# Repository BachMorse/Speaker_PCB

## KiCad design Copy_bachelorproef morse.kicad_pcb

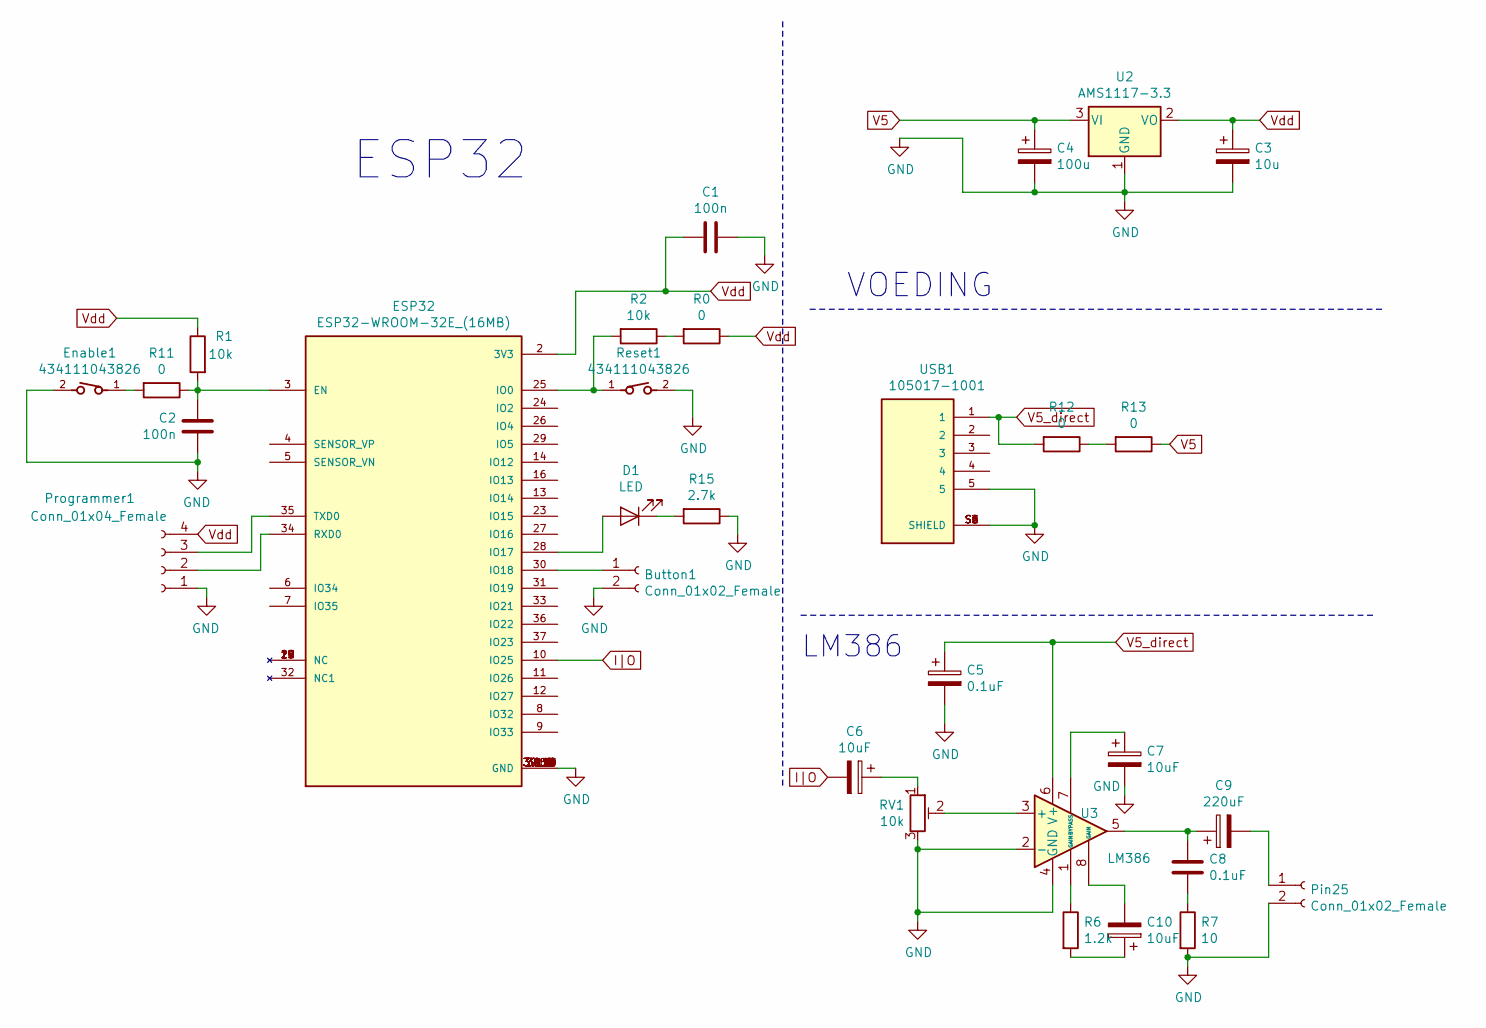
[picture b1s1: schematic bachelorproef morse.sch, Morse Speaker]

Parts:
Button1: Conn_01x02_Female; PinSocket_1x02_P2.54mm_Vertical
C1, C2: 100n; C_1206_3216Metric_Pad1.42x1.75mm_HandSolder
C3: 10u; C_1206_3216Metric_Pad1.42x1.75mm_HandSolder
C4: 100u; C_1206_3216Metric_Pad1.42x1.75mm_HandSolder
C5, C8: 0.1uF; C_1206_3216Metric_Pad1.42x1.75mm_HandSolder
C6, C7, C10: 10uF; C_1206_3216Metric_Pad1.42x1.75mm_HandSolder
C9: 220uF; C_1206_3216Metric_Pad1.42x1.75mm_HandSolder
D1: LED; R_1206_3216Metric_Pad1.42x1.75mm_HandSolder
ESP32: ESP32-WROOM-32E_(16MB); MODULE_ESP32-WROOM-32E_(16MB)
Enable1: 434111043826
Pin25: Conn_01x02_Female; PinSocket_1x02_P2.54mm_Vertical
Programmer1: Conn_01x04_Female; PinSocket_1x04_P2.54mm_Vertical
R0, R11, R12, R13: 0; R_1206_3216Metric_Pad1.42x1.75mm_HandSolder
R1, R2: 10k; R_1206_3216Metric_Pad1.42x1.75mm_HandSolder
R6: 1.2k; R_1206_3216Metric_Pad1.42x1.75mm_HandSolder
R7: 10; R_1206_3216Metric_Pad1.42x1.75mm_HandSolder
R15: 2.7k; R_1206_3216Metric_Pad1.42x1.75mm_HandSolder
RV1: 10k; Potentiometer_Bourns_3224G_Horizontal
Reset1: 434111043826
U2: AMS1117-3.3; SOT-223-3_TabPin2
U3: LM386; DIP794W45P254L959H508Q8
USB1: 105017-1001; MOLEX_105017-1001

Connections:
GND: Button1.2, C1.1, C2.2, C3.2, C4.2, C5.2, C7.2, ESP32.1 (GND), ESP32.15 (GND), ESP32.38 (GND), ESP32.39_1 (GND), ESP32.39_2 (GND), ESP32.39_3 (GND), ESP32.39_4 (GND), ESP32.39_5 (GND), ESP32.39_6 (GND), ESP32.39_7 (GND), ESP32.39_8 (GND), ESP32.39_9 (GND), ESP32.39_10 (GND), ESP32.39_11 (GND), ESP32.39_12 (GND), ESP32.39_13 (GND), ESP32.39_14 (GND), ESP32.39_15 (GND), ESP32.39_16 (GND), ESP32.39_17 (GND), ESP32.39_18 (GND), ESP32.39_19 (GND), ESP32.39_20 (GND), ESP32.39_21 (GND), Enable1.2, Pin25.2, Programmer1.1, R7.2, R15.1, RV1.3, Reset1.2, U2.1 (GND), U3.2 (-), U3.4 (GND), USB1.5, USB1.S1 (SHIELD), USB1.S2 (SHIELD), USB1.S3 (SHIELD), USB1.S4 (SHIELD), USB1.S5 (SHIELD), USB1.S6 (SHIELD)
I|O: C6.2, ESP32.10 (IO25)
unnamed: Button1.1, ESP32.30 (IO18)
unnamed: C2.1, ESP32.3 (EN), R1.2, R11.1
unnamed: C6.1, RV1.1
unnamed: C7.1, U3.7 (BYPASS)
unnamed: C8.1, C9.1, U3.5
unnamed: C8.2, R7.1
unnamed: C9.2, Pin25.1
unnamed: C10.1, R6.2
unnamed: C10.2, U3.8 (GAIN)
unnamed: D1.1 (K), R15.2
unnamed: D1.2 (A), ESP32.28 (IO17)
unnamed: ESP32.17 (NC), ESP32.18 (NC), ESP32.19 (NC), ESP32.20 (NC), ESP32.21 (NC), ESP32.22 (NC)
unnamed: ESP32.25 (IO0), R2.2, Reset1.1
unnamed: ESP32.34 (RXD0), Programmer1.2
unnamed: ESP32.35 (TXD0), Programmer1.3
unnamed: Enable1.1, R11.2
unnamed: R0.2, R2.1
unnamed: R6.1, U3.1 (GAIN)
unnamed: R12.1, R13.2
unnamed: RV1.2, U3.3 (+)
V5: C4.1, R13.1, U2.3 (VI)
V5_direct: C5.1, R12.2, U3.6 (V+), USB1.1
Vdd: C1.2, C3.1, ESP32.2 (3V3), Programmer1.4, R0.1, R1.1, U2.2 (VO)

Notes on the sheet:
ESP32
LM386
VOEDING

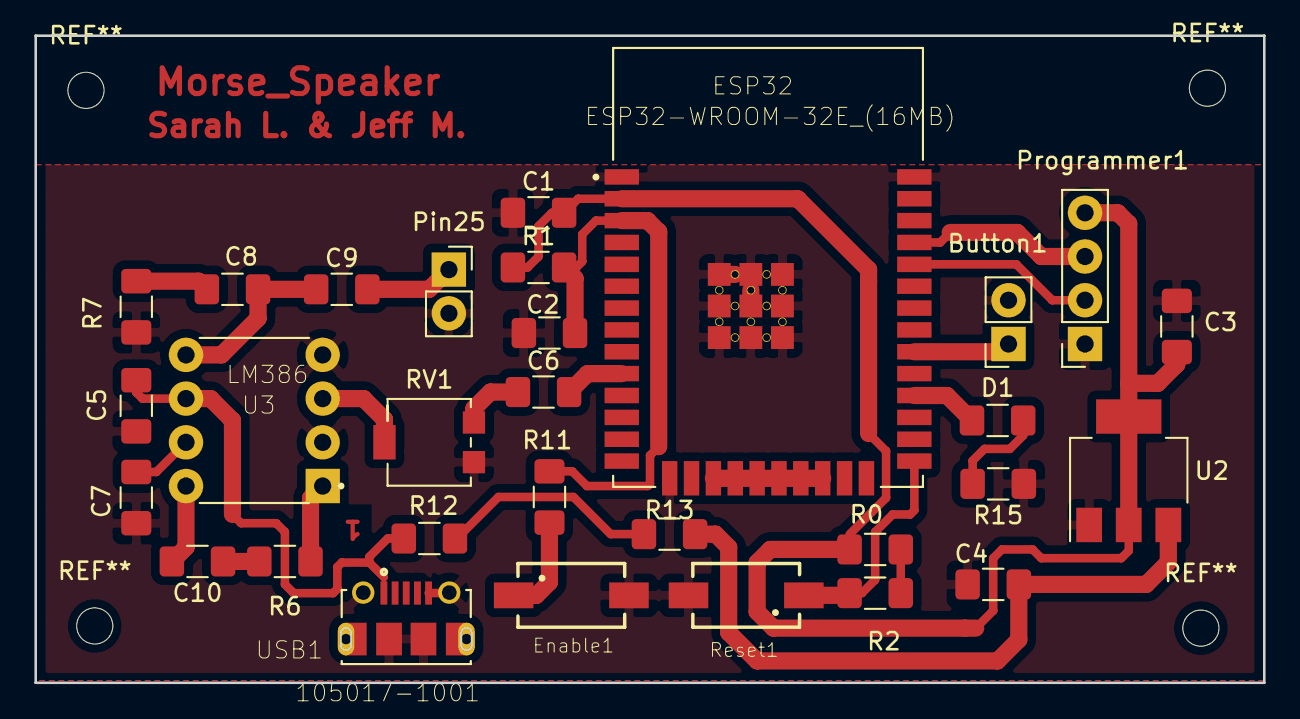
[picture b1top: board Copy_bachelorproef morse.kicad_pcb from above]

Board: 2 copper layers, 71.4 x 37.6 mm, 30 parts (0 on the bottom side), 25 nets.
